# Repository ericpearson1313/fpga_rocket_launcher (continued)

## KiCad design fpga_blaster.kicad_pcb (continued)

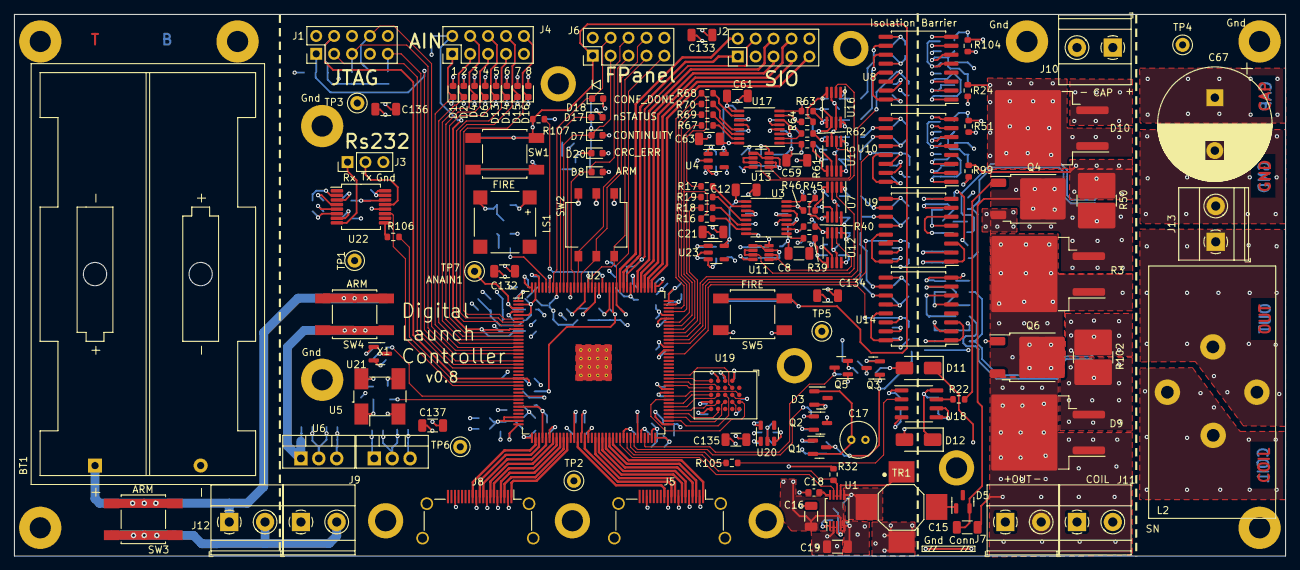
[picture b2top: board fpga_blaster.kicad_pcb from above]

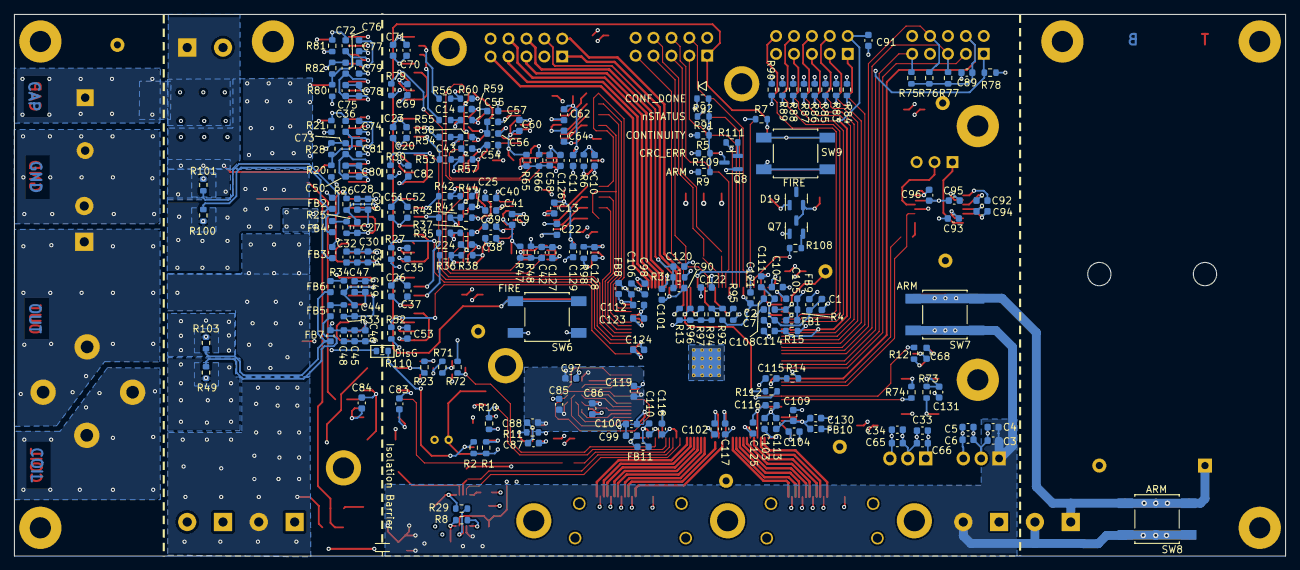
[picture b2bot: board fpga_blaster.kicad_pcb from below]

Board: 4 copper layers, 180.3 x 76.8 mm, 360 parts (221 on the bottom side), 238 nets.

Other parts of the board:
R3: 3K3 25W; TO-263-2_TabPin1

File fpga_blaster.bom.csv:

Qty,Reference(s),Value,DPN
1,BT1,~,36-2462-ND
25,"C1, C3, C5, C7, C10, C11, C18, C20, C26, C30, C34, C45, C50, C51, C66, C70, C75, C87, C88, C89, C90, C91, C128, C129, C130",1u,399-C0603C105K3RAC7867CT-ND
21,"C2, C23, C28, C31, C37, C38, C39, C40, C41, C47, C48, C52, C54, C55, C56, C57, C71, C74, C77, C78, C80",0.001u,399-C0603C102K3RAC7867CT-ND
8,"C4, C6, C27, C33, C36, C44, C65, C72",0.01u,399-C0603C103K3RAC7867CT-ND
6,"C8, C12, C21, C59, C61, C63",10u,399-C1206C106K4PAC7800CT-ND
66,"C9, C13, C14, C22, C24, C25, C29, C32, C35, C42, C43, C46, C49, C53, C58, C60, C62, C64, C68, C69, C73, C76, C79, C81, C82, C83, C84, C85, C86, C92, C93, C94, C95, C96, C97, C98, C99, C100, C101, C102, C103, C104, C105, C106, C107, C108, C109, C110, C111, C112, C113, C114, C115, C116, C117, C118, C119, C120, C121, C122, C123, C124, C125, C126, C127, C131",0.1u,399-C0603C104K3RAC7867CT-ND
1,C15,0.022u 630v,399-13296-1-ND
8,"C16, C19, C132, C133, C134, C135, C136, C137",4.7u,399-C1206C475K5PAC7800CT-ND
1,C17,100u 20v,1572-1659-ND
1,C67,100u 400V,1572-1041-ND
13,"D1, D2, D4, D6, D13, D14, D15, D16, D7, D8, D17, D18, D20",Yel,754-2039-1-ND
2,"D3, D19",BAV99,1655-BAV99CT-ND
1,D5,MMBD3004SE,GSD2004S-E3-08CT-ND
2,"D9, D10",‎STPSC10065G2,497-STPSC10065G2-TRCT-ND
2,"D11, D12",ES1J,1655-ES1JCT-ND
11,"FB1, FB2, FB3, FB4, FB5, FB6, FB7, FB8, FB9, FB10, FB11",Ferrite,490-5254-1-ND
4,"J1, J2, J4, J6",Conn_02x05_Odd_Even,732-2672-ND
1,J3,Conn_01x03,732-5316-ND
2,"J5, J8",HDMI_D_1.4,609-4614-1-ND
6,"J7, J9, J10, J11, J12, J13",Screw_Terminal_01x02,281-2888-ND
1,L2,390uH 5A,M8893-ND
1,LS1,Speaker,668-1068-1-ND
1,Q1,STR2P3LLH6(Pfet),497-15520-1-ND
4,"Q2, Q5, Q7, Q8",2N3904,4530-MMBT3904CT-ND
1,Q3,2N3906,4878-MMBT3906CT-ND
2,"Q4, Q6",IPD60R145,448-IPD60R145CFD7ATMA1CT-ND
12,"R1, R6, R7, R10, R11, R71, R72, R75, R76, R77, R95, R98",10K,P10.0KHCT-ND
3,"R2, R23, R32",100K,P100KHCT-ND
1,R3,3K3 25W,118-PWR263S-20-3301F-ND
14,"R4, R13, R14, R15, R24, R31, R49, R51, R99, R100, R101, R103, R104, R110",0R,P0.0GCT-ND
17,"R5, R9, R73, R78, R83, R84, R85, R86, R87, R88, R89, R90, R91, R92, R108, R109, R111",1K,P1.00KHCT-ND
1,R8,2K,P2.00KHCT-ND
21,"R12, R16, R17, R18, R19, R39, R40, R45, R46, R61, R62, R63, R64, R67, R68, R69, R70, R74, R105, R106, R107",22R,P22.0HCT-ND
4,"R20, R21, R80, R81",1.99M,541-MCT0603MD2004BP500CT-ND
5,"R22, R25, R26, R33, R34",10R,P10.0HCT-ND
4,"R27, R30, R52, R79",47K,P47KGCT-ND
6,"R28, R47, R48, R65, R66, R82",10.01K,10-ERA-3VRW1002VCT-ND
1,R29,51.1K,P51.1KDBCT-ND
8,"R35, R36, R41, R42, R53, R54, R55, R56",1.50K,P1.5KDBCT-ND
8,"R37, R38, R43, R44, R57, R58, R59, R60",3.01K,P3.01KDBCT-ND
2,"R50, R102",0.005R 1W,541-3275-1-ND
4,"SW1, SW3, SW4, SW5",FIRE,360-2595-1-ND
1,SW2,SW_DIP_x03,CT2193LPST-ND
7,"TP1, TP2, TP3, TP4, TP5, TP6, TP7",~,36-1037-ND
1,TR1,PA0367A,553-1978-1-ND
1,U1,LT3420,LT3420EMS#PBF-ND
1,U2,MAX10M04,544-3054-ND
2,"U3, U17",AD7352,505-AD7352BRUZ-ND
2,"U4, U23",TLV74325,296-48989-1-ND
1,U5,LMO78_03,3182-LMO78_03-1.0-ND
1,U6,4945,2183-4945-ND
4,"U7, U12, U15, U16",LTC6362,505-LTC6362CMS8#PBF-ND
2,"U8, U10",AMC3330,296-AMC3330QDWERQ1CT-ND
2,"U9, U14",AMC3302,296-AMC3302DWERCT-ND
2,"U11, U13",TLV9062xD,296-TLV9062IDDFRCT-ND
1,U18,IR2127,IR2127SPBFCT-ND
1,U19,S80KS2563GABHV020,448-S80KS2563GABHV020-ND
1,U20,TLV74318,296-48712-1-ND
1,U21,LM809,LM809M3-2.63/NOPBCT-ND
1,U22,MAX3227,296-19849-1-ND
1,X1,ASE-48MHz,535-9328-1-ND

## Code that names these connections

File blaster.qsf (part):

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set_location_assignment PIN_131 -to iset[2]
set_location_assignment PIN_132 -to arm_led_n
set_location_assignment PIN_135 -to cont_led_n
set_location_assignment PIN_140 -to speaker
set_location_assignment PIN_141 -to speaker_n
set_location_assignment PIN_62 -to lt3420_charge
set_location_assignment PIN_64 -to lt3420_done
set_location_assignment PIN_28 -to reset_n
set_location_assignment PIN_65 -to pwm
set_location_assignment PIN_69 -to cont_n
set_location_assignment PIN_66 -to dump
set_location_assignment PIN_106 -to ad_cs
set_location_assignment PIN_102 -to ad_sdata_a[1]
set_location_assignment PIN_99 -to ad_sdata_a[0]
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set_location_assignment PIN_75 -to spi8_data_pad[2]
set_location_assignment PIN_85 -to spi8_data_pad[1]
set_location_assignment PIN_78 -to spi8_data_pad[0]
set_location_assignment PIN_74 -to spi_ds
set_location_assignment PIN_81 -to spi_ncs
set_location_assignment PIN_87 -to spi_clk0
set_location_assignment PIN_101 -to ad_sclk
set_location_assignment PIN_96 -to CIdiag
set_location_assignment PIN_97 -to CVdiag
set_location_assignment PIN_93 -to LIdiag
set_location_assignment PIN_98 -to LVdiag
set_location_assignment PIN_39 -to hdmi_ck
set_location_assignment PIN_38 -to "hdmi_ck(n)"
set_location_assignment PIN_43 -to hdmi_d0
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set_location_assignment PIN_57 -to "hdmi2_d1(n)"
set_location_assignment PIN_60 -to hdmi2_d2
set_location_assignment PIN_59 -to "hdmi2_d2(n)"
set_location_assignment PIN_80 -to spi_nrst
set_global_assignment -name ENABLE_OCT_DONE OFF
set_global_assignment -name ENABLE_BOOT_SEL_PIN OFF
set_global_assignment -name USE_CONFIGURATION_DEVICE ON
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
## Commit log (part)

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2024-11-11 link typo
2024-11-13 fire button activates PWM 1usec/1000usec
2024-11-14 Add explicit ioe pad for digio
2024-11-14 Fixed up keypad to detect 4 cycles with no contact closure
2024-11-16 SPI8 registered IOE, and latch enable and read data path
2024-11-17 PScontroller complied and integrated into the chip.
2024-11-18 fixup typo's (maybe fix bug?)
2024-11-18 Change back to full chip synthesis
2024-11-18 Added Extra cycle hidden in READ_ID. todo add to ALL? other transactions with latency
2024-11-18 Upgraded to a mix/max accumulator for vga scope
2024-11-19 tried to add a delay to make diag errors (0's) more visible. not great, works for now
2024-11-20 PSRAM reads (un-init data) look like their working with random fixed pattern.
2024-11-20 logic fixes
2024-11-20 Connected AXI write ports on sram
2024-11-21 Delay the ADC sample window 1 cycle for full 12 bit capture
2024-11-21 Corrected write data alignment adding wdata input reg
2024-11-25 Added 800x480 video mode (60hz @ 33.26 Mhz)
2024-11-25 Chnage over to 800x480 using 32Mhz/160Mhz for hmdi clk/clk5
2024-11-26 A Digikey fastcart link BOM v0.8 (before ECO and missing pololu dc/dc)
2024-12-07 Updates ascii font generator to use 1 hot x y gating within the 5x7 char and Reduction-OR (for the win)
2024-12-09 mis typed reduction-OR
2024-12-09 Invert continuity panel LED.
2024-12-12 Adjust vertical offset for PWM on waceform display
2024-12-12 Clip current to zero and direction to be aligned with PWM to limit drift
2024-12-14 Tweak model
2024-12-15 add running operation photos
2024-12-15 Added a VGA string overlay module, and convereted the vga wage trace funciton over too it.
2024-12-16 Added Hex and binary overlay generators.
2024-12-16 define wires to stop warnings
2024-12-16 Added full resolution B1 trace to get full visibility.
2024-12-20 Add a resistance calc and integrate (over-ride capI-b0)
2024-12-28 acucmulated notes of changes and fixes done for the v0.8 iPCB
2024-12-28 Renamved photos and MD formating
2025-01-02 wired up '(' key to genrate a 2.6usec pwm pulse, 1ms repeat
2025-01-08 Added testbench and used it to confirmed that Resistance ouput is a clipped 6.5 format
2025-01-09 Added 1.3 sec display read from sram. Commented out, will use later, but good looking
2025-01-09 With the trimmed inputs the model started to drift. Hacked in some deadzones for now. This does not fix it.
2025-01-09 Fixed comment on clamp testcase
2025-01-12 PWM controlled by current feedback with min 1 pulse and max 16 usec high. .(just a 3 cycle experiment)
2025-01-14 Restored display of B0 trace (was temp driven by R=E/I resistance plot)
2025-01-16 Added 3E.E (62.9) ohms as open circuit indication. (or no cap voltage), and single-shot operation debounce.
2025-01-16 tweak the tiny scope ram usage (now collides at LE usage)
2025-01-18 First run with model feedback. 3 cycle pwm operation. Wish I could record a photo with this commit.
2025-01-19 Added ramp flag for min pulses until the first time we've seen current over the min tolerance. Flatest so far.
2025-01-20 note on current input filter resistors
2025-01-20 Chnage model output bits
2025-01-20 removed ramp, tested for -ve est, min pulse with 4us, tiny scope and ohm reading moved to port 2
2025-01-21 first captured copperhead shows burnthrough
2025-01-22 Resistance calculation included a long ~1s holdoff and includes updating continuity led and has coded tone outputs
2025-01-23 Add power accumulate flag to resistance measurement unit to accumulate power delivered to igniter during resistance pulse
2025-01-23 Added Pulse energy as integral of cap and output power (sum of I*V samples). operates for resistance and firing pulses
2025-01-24 tweaked resistance reading to better realiably read open circuits.
2025-01-24 Limit battery current in RUN mode by holding hdmi encoder in reset until we've finished charging.
2025-01-27 Igniter burthrough detect, if after seeing 0.5A then see 0. current falls < 150 mA while still having 100 Volts in the cap. Burn through detect discontinues pulse initiation (todo terminate current p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
2025-01-28 Centered zoom, added burnthrough on vout>vcap, turned off some text saves logic (99%->97%)
2025-02-01 Horizontal scale text changes with zoom
2025-02-02 Fix post fire setting of burn flag
2025-02-02 stop energy accumulation upon burn detect. Try to improve robust fire button (ie fire flag not set during fire sequence)
2025-02-08 debounce and beep for fire button. Still crap (on button release!)
2025-02-08 Fixed up formatting of re-init data from adc to model. Seems to be behaving ...
2025-02-12 Lesson Learned "the MAX10SC-compact devices do not support Memory Initialization" needed for the text overlay. Un-integrated from chip at this time, sigh
2025-02-13 change over to text overlay, with PLL update and flash changes
2025-02-13 fixed up color and text packing order in rom
2025-02-13 some debugging of overlay
2025-02-14 Flash rom update on text color packing in rom
2025-02-14 text overlay updates
2025-02-14 Changed , to upper bar in font. And fixed up verillog for simulator that generates the font rom init txt file
2025-02-15 SW1 disables model feedback into control loop (will just use ADC current feedback, proves it controls current in model-gone-crazy situations)
2025-02-19 Added text chars, Updated font file, ran sim, editted overlay. Commit to gen mif file
2025-02-19 Moving special chars into 7-bit ASCII space. Unicode handling during rom building is needed.
2025-02-19 text overlay update
2025-03-04 Added Read BL=32 burst support in addition to default of 4.
2025-03-04 Fixed width of ohm mult input, no effect
2025-03-06 Added 2nd araddr read address port to sram
2025-03-06 re-wrote key debounce, rel 100ms, long 600ms
2025-03-07 Moved Beep legend
2025-03-08 filter in the flow to embed the git commit 7 digit hash into the video overlay. Part of the command: git rev-parse HEAD | head -c7 | basenc --base2msbf --wrap=8 | awk -f format_commit.awk
2025-03-21 Basic updates to README.md
2025-03-22 Fix some typos, then added some more...
2025-03-26 Added HDMI encodings for videoguard, data guard and island encoding
2025-03-27 added excellent HDMI InfoFrame utilities found in https://github.com/hdl-util/hdmi.git
2025-03-27 To save $500. Dynamically switch HDMI to YUV2 during blipvert to use cheap $20 USB capture dongles supporting lossless driverless YUV2 capture
2025-03-30 Fixed hdmi encoding logic issue. no ext lib. down to 96% utilized. timing closed
2025-04-01 Built rom for text update
2025-05-02 Add release pof
2025-05-24 Added a forge chip wrapper. Allows adding logging/plotting in Max10 emulation chip
2025-05-24 both quartus and forge build without severe errors
2025-05-25 Port updates to connect LAC clock generation
2025-05-25 remove arm button from emulation interface
2025-05-25 Replace resistance based continuity with simple IVmax circuit. Compiles 96% ultil 23 Mhz so far
2025-05-26 Shorten manual pulse test to 3 pulses
2025-05-26 Tried reset-less mode. not working in emulation with sof load. tried initial statements,, improved (blink) but no more action
2025-05-29 Simplified burnthrough to trigger if deltaV > 24V/us.
2025-06-05 Revert "Simplified burnthrough to trigger if deltaV > 24V/us."
    This reverts commit 615e04b294d4fd2ba8a925b19df2fbe28992f398.
2025-06-12 3D printed models to test handheld suitability
    With ideally 4x AA (but 2x maybe), 2 capacitors, and a coil, with 2 buttons and 2 leds. Tried 6 different arrangements of components to see which was the best fit for a handheld device.
2025-06-17 Landscape style PCB initial layout 3d. Large components on bottom as per model. Forge emulator connector section of PCB can be cut away, but also has a spare fpga land point.
2025-06-17 Update README.md
    Hard truth about cap discharge launchers.
2025-06-22 Add Estes controller (approximate) schematic
2025-07-03 Landscape handheld prototype 3dprinted prior to detailed PCB design. It will influence the detailed pcb layout.
2025-07-23 Step to 6 amps at 20 msec. Globalized system contants out of forge fpge. Parameterize current setpoint timing.
2025-08-25 Update README.md, move updates to bottom as they are evolving into another repo..
2026-02-27 I/O connection sanitized. one-time power on reg circuit
2026-02-27 Removed unsupported int cast, sigh!
2026-02-27 full launch cycle starting to run
2026-02-28 Update wrapper to match core
2026-02-28 handle small vcap clipping correctly
2026-02-28 Switch over to positive ADC values, disconnect reset
2026-03-01 change a0,b0 nomenclature to actual
2026-03-01 re-update wrapper to match port name changes
2026-03-02 Min changes for EB. I/O polarity, deprecate lt3420_done, use adc of vcap instead
2026-03-11 Parameterize and shorten vga_scope buffer. Save M9Ks for binary scope
2026-03-11 Added lcc_mon[7:0] into the large PSRAM circular buffer (hiding in analog LSBs and display function, almost working
2026-03-13 Revert "back annotate ad negation fix to lcc"
    This reverts commit fd8ec08d62c2ac43ee7cae56a2d31e676d817087.
2026-03-24 Started splitting out analyser monitor functions. Start with just receving adc data (no controlling)
2026-03-25 Update to ca91a70 tested logic: 320v, and 100v/us and burn test
2026-03-29 Continue to split out analyser funcitonality accessing only LCC I/O pins.
2026-03-29 Update ovderlay text for LCC monitor
2026-03-30 rebuilt adjusted overlay
2026-03-31 Remove 2nd HDMI port (as its not connected on the PCB). Same with adc diag signals
2026-04-01 integrate and update lcc core into emulator/analyser framework. No internal probes
2026-04-01 Turn on emulator and resolve analyzer missing declarations.
2026-04-01 Update project file for updated ref frequncy
2026-04-01 Use internal 50 Mhz osc for PLL ref
2026-04-02 remove reset from LCC core (as per real device), operation after initial state was updated
2026-04-06 Add clock domain crossing for analyzer to move data from sclk to clk. Updated SDC.
2026-04-07 Update ADC inputs to registered schmitt inputs
2026-04-09 updated I/O timing, still not satisfactory. Will build in a scope to see raw input signals
2026-04-09 Scope allowed me to see the signals. The sclk is not usable for clocking logic, but oversampleing the cs and sdata bus should work.
2026-04-10 Add generated clocked input register
2026-04-12 Increase drive strength on sclk an cs on 1k fpga
2026-04-12 increase drive on cs, sclk to 2ma.
2026-04-13 Lcc 1k Turned on auto run. ad_cs output reg. lcc mon ADC is good. issue: just pulses charge and stops charging..
2026-04-15 fixed top level (unsimulated!) adc input mapping
2026-04-16 hacked/tested. Its all about initialization. re-wrote to remove most reset controls. basically running for first time.
2026-04-17 Allow monitor capture halt to be retrigged by another cycle (use early charge)
2026-04-18 Tapeout V1 bitstream artefacts
2026-04-27 roughing in the L-C-R models
2026-04-28 system simulation starting to match FP sim numbers, almost
2026-04-28 added in synthesiable adc simulation
2026-04-29 Have sim testbench generate the rom init with ()
2026-04-29 Integrated system simulation fpga, compiles.
2026-04-29 floated the ad serial data lines, will model system from raw inputs. Fpga tested, working but some bugs to fix.
2026-04-30 Updated system simulator overlay
2026-04-30 Put cap energy from sim into main display channel.
2026-05-04 Add Tiny Tapeout top level project.v
2026-05-04 Support init cap charge for shorter charge time
2026-05-04 Icarus testbench starting to run with precharged cap to make run time reasonable, ms vs sec
2026-05-05 real tt test running and passing
2026-05-05 Moved syssim.sv to test dir and include it in tb.v
2026-05-05 Updated for moved syssim.sv
2026-05-05 try reformat 64x16b rom to make it smaller?
2026-05-06 self test version starting to run sim
2026-05-07 BIST running and passing
2026-05-07 bitwidth for parameters to help synth
2026-05-07 Have both SYSTEM and BIST tests for GL sims
2026-05-07 For gate level sims need to include syssim.sv
2026-05-08 turn off dump model, as not used in the short/self tests
2026-05-08 Make BIST thresholds continuous and tighter
2026-05-09 Tighten test asserts
2026-05-10 Tighten BIST a tiny bit more
